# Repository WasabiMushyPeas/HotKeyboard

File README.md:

# HotKey board
This is a simple Arduino project that allows Arduino boards that don't support Arduino's HID library to simulate key presses through a serial monitor accessed by python which than simulates the key presses. This repo also includes a PCB that connects 9 keyboard switches status LEDs and a DIP switch.
# Installation
- Download this git repo
- upload the [hotKeyBoard.ino](https://github.com/WasabiMushyPeas/HotKeyboard/blob/main/hotKeyBoard.ino) to your Arduino through the [Arduino IDE](https://www.arduino.cc/en/software)
- Pip install these Python libraries
`
pip install input
`
`
pip install serial
`
- make sure ser = serial. Serial('/dev/ttyACM0') in [keyBoardInterpriter.py](https://github.com/WasabiMushyPeas/HotKeyboard/blob/main/keyBoardInterpriter.py) on line 12 you replace '/dev/ttyACM0' with the port that your Arduino is connected to
- then run the python program
# Customization
if you want to customize your keyboard shortcuts edit the [keyBoardShortcuts.txt](https://github.com/WasabiMushyPeas/HotKeyboard/blob/main/keyBoardShortcuts.txt) and put your keyboard shortcuts in the text file like so:
```
cmd|g #cmd is short for the windows key or the command key on mac
Ctrl|h #this the command Ctrl+h | separates the key presses
Ctrl|Alt|Delete #This will be bound to the 3rd key and Ctrl|h the 2nd key and cmd|g the 1st key you can put up to 27. 
#The first key is the top left going from left to right then up to down.
```
> :warning: **Make sure you delete all the comments in [keyBoardShortcuts.txt](https://github.com/WasabiMushyPeas/HotKeyboard/blob/main/keyBoardShortcuts.txt) can not have comments**
# Other
if you need to excute commands on linux check out [the awesomewm branch](https://github.com/WasabiMushyPeas/HotKeyboard/tree/awesomewm)

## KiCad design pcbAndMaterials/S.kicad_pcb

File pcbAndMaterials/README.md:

# Custom PCB
if you would like to use my PCB design you need:
  - 0805 1k and 500ohm resistors and LEDs and 1uf capacitors
  - Arduino nano BLE
  - DIP switch with four switches
  - Cherry MX switches

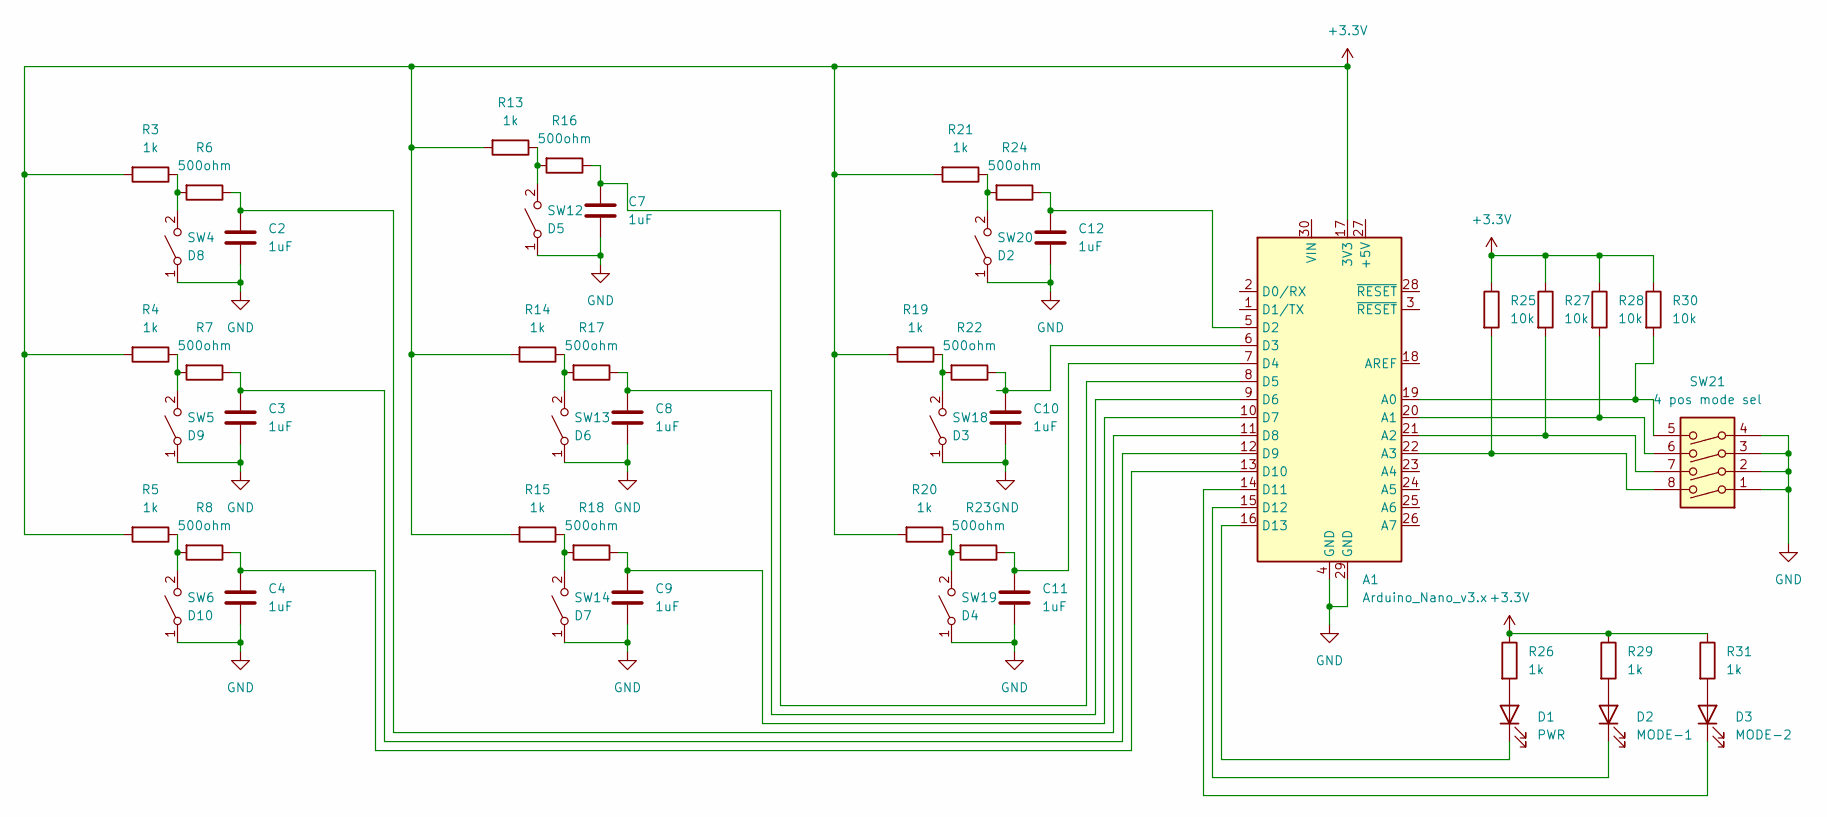
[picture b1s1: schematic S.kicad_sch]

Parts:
A1: Arduino_Nano_v3.x; Arduino_Nano
C2, C3, C4, C7, C8, C9, C10, C11, C12: 1uF; C_0805_2012Metric_Pad1.18x1.45mm_HandSolder
D1: PWR; LED_0805_2012Metric_Pad1.15x1.40mm_HandSolder
D2: MODE-1; LED_0805_2012Metric_Pad1.15x1.40mm_HandSolder
D3: MODE-2; LED_0805_2012Metric_Pad1.15x1.40mm_HandSolder
R3, R4, R5, R13, R14, R15, R19, R20, R21, R26, R29, R31: 1k; R_0805_2012Metric_Pad1.20x1.40mm_HandSolder
R6, R7, R8, R16, R17, R18, R22, R23, R24: 500ohm; R_0805_2012Metric_Pad1.20x1.40mm_HandSolder
R25, R27, R28, R30: 10k; R_0805_2012Metric_Pad1.20x1.40mm_HandSolder
SW4: D8; SW_Cherry_MX_1.00u_PCB
SW5: D9; SW_Cherry_MX_1.00u_PCB
SW6: D10; SW_Cherry_MX_1.00u_PCB
SW12: D5; SW_Cherry_MX_1.00u_PCB
SW13: D6; SW_Cherry_MX_1.00u_PCB
SW14: D7; SW_Cherry_MX_1.00u_PCB
SW18: D3; SW_Cherry_MX_1.00u_PCB
SW19: D4; SW_Cherry_MX_1.00u_PCB
SW20: D2; SW_Cherry_MX_1.00u_PCB
SW21: 4 pos mode sel; DIP-8_W7.62mm

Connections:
+3V3: A1.17 (3V3), R3.2, R4.2, R5.2, R13.2, R14.2, R15.2, R19.2, R20.2, R21.2, R25.1, R26.1, R27.1, R28.1, R29.1, R30.1, R31.1
GND: A1.4 (GND), A1.29 (GND), C2.2, C3.2, C4.2, C7.2, C8.2, C9.2, C10.2, C11.2, C12.2, SW4.1 (A), SW5.1 (A), SW6.1 (A), SW12.1 (A), SW13.1 (A), SW14.1 (A), SW18.1 (A), SW19.1 (A), SW20.1 (A), SW21.1, SW21.2, SW21.3, SW21.4
unnamed: A1.5 (D2), C12.1, R24.1
unnamed: A1.6 (D3), C10.1, R22.1
unnamed: A1.7 (D4), C11.1, R23.1
unnamed: A1.8 (D5), C7.1, R16.1
unnamed: A1.9 (D6), C8.1, R17.1
unnamed: A1.10 (D7), C9.1, R18.1
unnamed: A1.11 (D8), C2.1, R6.1
unnamed: A1.12 (D9), C3.1, R7.1
unnamed: A1.13 (D10), C4.1, R8.1
unnamed: A1.14 (D11), D3.1 (K)
unnamed: A1.15 (D12), D2.1 (K)
unnamed: A1.16 (D13), D1.1 (K)
unnamed: A1.19 (A0), R30.2, SW21.5
unnamed: A1.20 (A1), R28.2, SW21.6
unnamed: A1.21 (A2), R27.2, SW21.7
unnamed: A1.22 (A3), R25.2, SW21.8
unnamed: D1.2 (A), R26.2
unnamed: D2.2 (A), R29.2
unnamed: D3.2 (A), R31.2
unnamed: R3.1, R6.2, SW4.2 (B)
unnamed: R4.1, R7.2, SW5.2 (B)
unnamed: R5.1, R8.2, SW6.2 (B)
unnamed: R13.1, R16.2, SW12.2 (B)
unnamed: R14.1, R17.2, SW13.2 (B)
unnamed: R15.1, R18.2, SW14.2 (B)
unnamed: R19.1, R22.2, SW18.2 (B)
unnamed: R20.1, R23.2, SW19.2 (B)
unnamed: R21.1, R24.2, SW20.2 (B)

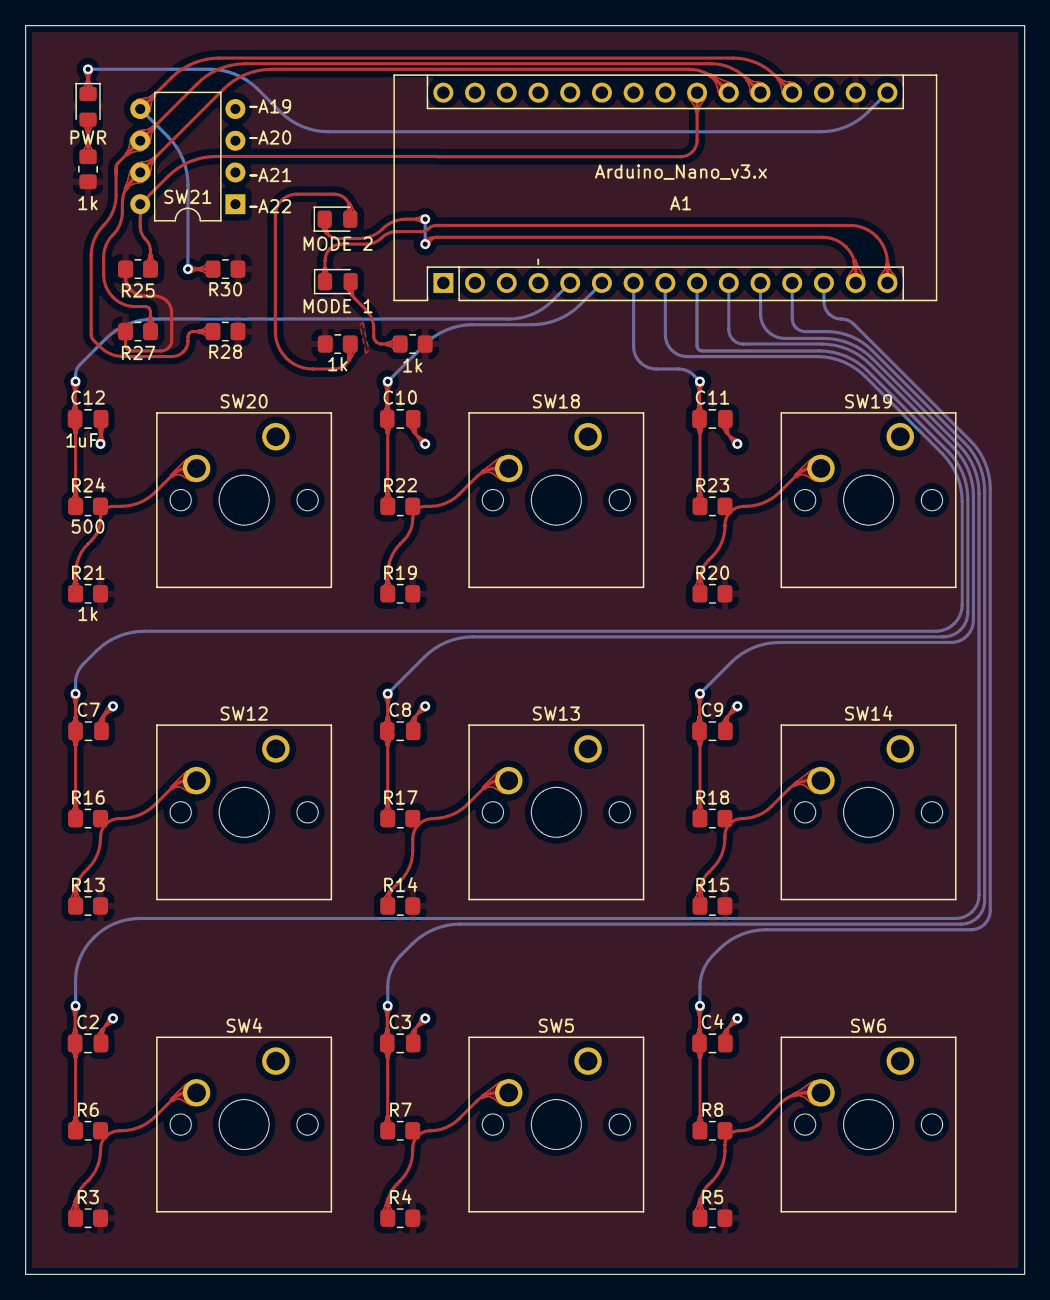
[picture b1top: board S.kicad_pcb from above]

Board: 2 copper layers, 80.0 x 100.0 mm, 48 parts (0 on the bottom side), 30 nets.

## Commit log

2022-07-10 adding python program
2022-07-10 added arduino file
2022-07-12 updated py file to include 27 keys
2022-07-12 allows dip switch 1 to turn off key board output
2022-07-12 allow dip switch 1 to turn off keyboard output
2022-07-12 change keyboard command layout
    turned mode 2 into just commands and mod 1 and 3 into just key presses
2022-07-12 added readme file
    going to add the main readme in the main branch with more info
2022-07-12 unfinished readme file
    need to finish Customization section and run everything through spell check
2022-07-12 finished readme
2022-07-12 Added pcbAndMaterials folder with a readme file
2022-07-12 added the pcb files
2022-07-12 Added renders of the pcb
2022-07-12 very basic readme
    need to update
2022-07-14 real pcb pic
2022-07-24 bug fix with dip 1
    Fixed a bug that happened when the Arduino read the inverse of dip switch 1 which controls if the key board outputs anything or not.
2022-07-24 Fix bug and added listener
    Fix a bug with dip switch 1 and add a listener that starts the main program when keyboard plugged in.
2022-07-24 Nothing Changed with these
2022-07-24 Fixed bug with dip switch 1
2022-07-24 Fix bug on dip 1
2023-01-05 Updated read me
